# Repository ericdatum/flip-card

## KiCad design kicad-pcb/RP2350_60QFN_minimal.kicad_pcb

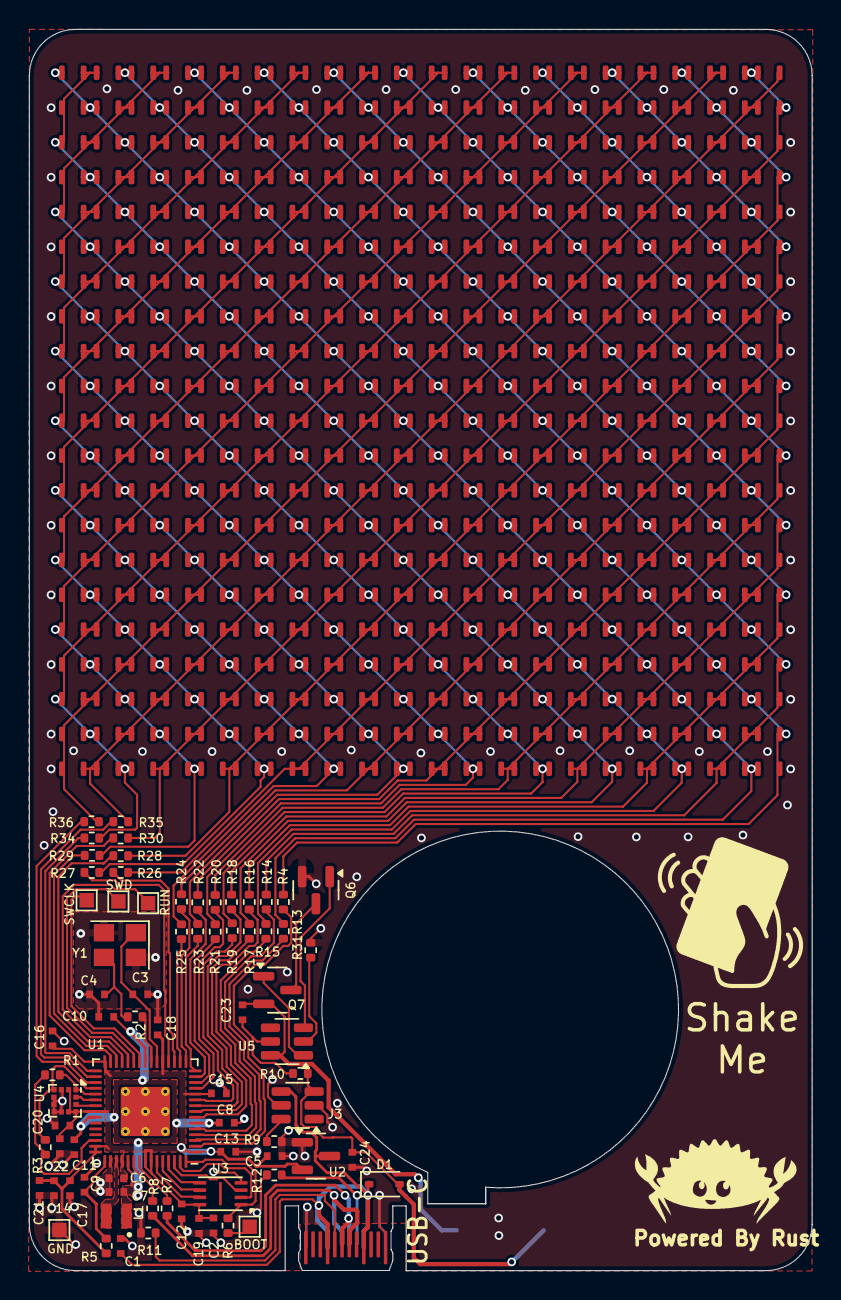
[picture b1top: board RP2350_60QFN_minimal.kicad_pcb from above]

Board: 2 copper layers, 54.0 x 85.6 mm, 517 parts (0 on the bottom side), 82 nets.

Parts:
BOOT: TestPoint; TestPoint_Pad_1.0x1.0mm
BT1: Battery_Cell; BatteryHolder_Custom
C1, C5, C24: 1u; C_0402_1005Metric_small_pads
C2, C8, C11, C12, C13, C14, C15, C16, C17, C18, C20, C21, C23: 100n; C_0402_1005Metric_small_pads
C3, C4: 15p; C_0402_1005Metric_small_pads
C6, C7, C9, C10: 4.7u; C_0402_1005Metric_small_pads
C19, C22: 10u; C_0402_1005Metric_small_pads
D1: Schottky Diode; D_SOD-323
D101, D102, D103, D104, D105, D106, D107, D108, D109, D110, D111, D112, D113, D114, D115, D116, D117, D118, D119, D120, D121, D122, D123, D124, D125, D126, D127, D128, D129, D130, D131, D132, D133, D134, D135, D136, D137, D138, D139, D140, D141, D142, D143, D144, D145, D146, D147, D148, D149, D150, D151, D152, D153, D154, D155, D156, D157, D158, D159, D160, D161, D162, D163, D164, D165, D166, D167, D168, D169, D170, D171, D172, D173, D174, D175, D176, D177, D178, D179, D180, D181, D182, D183, D184, D185, D186, D187, D188, D189, D190, D191, D192, D193, D194, D195, D196, D197, D198, D199, D200, D201, D202, D203, D204, D205, D206, D207, D208, D209, D210, D211, D212, D213, D214, D215, D216, D217, D218, D219, D220, D221, D222, D223, D224, D225, D226, D227, D228, D229, D230, D231, D232, D233, D234, D235, D236, D237, D238, D239, D240, D241, D242, D243, D244, D245, D246, D247, D248, D249, D250, D251, D252, D253, D254, D255, D256, D257, D258, D259, D260, D261, D262, D263, D264, D265, D266, D267, D268, D269, D270, D271, D272, D273, D274, D275, D276, D277, D278, D279, D280, D281, D282, D283, D284, D285, D286, D287, D288, D289, D290, D291, D292, D293, D294, D295, D296, D297, D298, D299, D300, D301, D302, D303, D304, D305, D306, D307, D308, D309, D310, D311, D312, D313, D314, D315, D316, D317, D318, D319, D320, D321, D322, D323, D324, D325, D326, D327, D328, D329, D330, D331, D332, D333, D334, D335, D336, D337, D338, D339, D340, D341, D342, D343, D344, D345, D346, D347, D348, D349, D350, D351, D352, D353, D354, D355, D356, D357, D358, D359, D360, D361, D362, D363, D364, D365, D366, D367, D368, D369, D370, D371, D372, D373, D374, D375, D376, D377, D378, D379, D380, D381, D382, D383, D384, D385, D386, D387, D388, D389, D390, D391, D392, D393, D394, D395, D396, D397, D398, D399, D400, D401, D402, D403, D404, D405, D406, D407, D408, D409, D410, D411, D412, D413, D414, D415, D416, D417, D418, D419, D420, D421, D422, D423, D424, D425, D426, D427, D428, D429, D430, D431, D432, D433, D434, D435, D436, D437, D438, D439, D440, D441, D442, D443, D444, D445, D446, D447, D448, D449, D450, D451, D452, D453, D454, D455, D456, D457, D458, D459, D460, D461, D462, D463, D464, D465, D466, D467, D468, D469, D470, D471, D472, D473, D474, D475, D476, D477, D478, D479, D480, D481, D482, D483, D484, D485, D486, D487, D488, D489, D490, D491, D492, D493, D494, D495, D496, D497, D498, D499, D500, D501, D502, D503, D504, D505, D506, D507, D508, D509, D510, D511, D512, D513, D514, D515, D516, D517, D518, D519, D520, D521, D522, D523, D524, D525, D526, D527, D528, D529, D530, D531, D532, D533, D534, D535, D536, D537, D538, D539, D540, D541: LED; LED_0603_1608Metric
GND: TestPoint; TestPoint_Pad_1.0x1.0mm
J1: USB_C_Receptacle_USB2.0_14P; USB_C_PADDLE
J3: TP4057; SOT-23-6
L1: 3.3u; L_pol_2016
Q6, Q7: HL-2302V; SOT-23
R1, R3, R11, R12: 5K1; R_0402_1005Metric
R2, R6, R31: 1K; R_0402_1005Metric
R4, R13, R14, R15, R16, R17, R18, R19, R20, R21, R22, R23, R24, R25, R26, R27, R28, R29, R30, R34, R35, R36: 22; R_0402_1005Metric
R5: 33; R_0402_1005Metric
R7, R8: 27; R_0402_1005Metric
R9: 20K; R_0402_1005Metric
R10: 100; R_0402_1005Metric
RUN: TestPoint; TestPoint_Pad_1.0x1.0mm
SWCLK: TestPoint; TestPoint_Pad_1.0x1.0mm
SWD: TestPoint; TestPoint_Pad_1.0x1.0mm
U1: RP2350A; RP2350-QFN-60-1EP_7x7_P0.4mm_EP3.4x3.4mm_ThermalVias
U2: REG_3.3V; SOT-23
U3: ZD25WQ32CEIGR; Winbond_USON-8-1EP_3x2mm_P0.5mm_EP0.2x1.6mm
U4: LIS2DH12TR; LGA-12_2x2mm_P0.5mm
U5: DW01A; SOT-23-6
Y1: ABM8-272-T3; Crystal_SMD_3225-4Pin_3.2x2.5mm

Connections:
+1V1: C7.1, C8.1, C10.1, C11.1, L1.1, U1.6 (DVDD), U1.23 (DVDD), U1.39 (DVDD), U1.50 (VREG_FB)
+3V3: C2.1, C5.1, C6.1, C12.1, C13.1, C14.1, C15.1, C16.1, C17.1, C18.1, C19.1, C20.2, C21.2, C22.1, R5.1, U1.1 (IOVDD), U1.11 (IOVDD), U1.20 (IOVDD), U1.30 (IOVDD), U1.38 (IOVDD), U1.44 (ADC_AVDD), U1.45 (IOVDD), U1.49 (VREG_VIN), U1.53 (USB_OTP_VDD), U1.54 (QSPI_IOVDD), U2.2 (VO), U3.8 (VCC), U4.2 (CS), U4.9 (VDD), U4.10 (VDD_IO)
/FLASH_SS: R6.1, U1.60 (QSPI_SS), U3.1 (~CS)
/LED_ARRAY/D1: D101.1 (K), D102.1 (K), D103.2 (A), D124.1 (K), D125.2 (A), D146.1 (K), D147.2 (A), D168.1 (K), D169.2 (A), D190.1 (K), D191.2 (A), D212.1 (K), D213.2 (A), D234.1 (K), D235.2 (A), D256.1 (K), D257.2 (A), D278.1 (K), D279.2 (A), D300.1 (K), D301.2 (A), D322.1 (K), D323.2 (A), D344.1 (K), D345.2 (A), D366.1 (K), D367.2 (A), D388.1 (K), D389.2 (A), D410.1 (K), D411.2 (A), D432.1 (K), D433.2 (A), D454.1 (K), D455.2 (A), D476.1 (K), D477.2 (A), D498.1 (K), D499.2 (A), D520.1 (K), R36.1
/LED_ARRAY/D2: D101.2 (A), D122.1 (K), D123.2 (A), D144.1 (K), D145.2 (A), D166.1 (K), D167.2 (A), D188.1 (K), D189.2 (A), D210.1 (K), D211.2 (A), D232.1 (K), D233.2 (A), D254.1 (K), D255.2 (A), D276.1 (K), D277.2 (A), D298.1 (K), D299.2 (A), D320.1 (K), D321.2 (A), D342.1 (K), D343.2 (A), D364.1 (K), D365.2 (A), D386.1 (K), D387.2 (A), D408.1 (K), D409.2 (A), D430.1 (K), D431.2 (A), D452.1 (K), D453.2 (A), D474.1 (K), D475.2 (A), D496.1 (K), D497.2 (A), D518.1 (K), D519.2 (A), D540.1 (K), D541.2 (A), R35.1
/LED_ARRAY/D3: D102.2 (A), D103.1 (K), D104.1 (K), D105.2 (A), D122.2 (A), D123.1 (K), D126.1 (K), D127.2 (A), D143.1 (K), D148.1 (K), D149.2 (A), D170.1 (K), D171.2 (A), D192.1 (K), D193.2 (A), D214.1 (K), D215.2 (A), D236.1 (K), D237.2 (A), D258.1 (K), D259.2 (A), D280.1 (K), D281.2 (A), D302.1 (K), D303.2 (A), D324.1 (K), D325.2 (A), D346.1 (K), D347.2 (A), D368.1 (K), D369.2 (A), D390.1 (K), D391.2 (A), D412.1 (K), D413.2 (A), D434.1 (K), D435.2 (A), D456.1 (K), D457.2 (A), D478.1 (K), R34.1
/LED_ARRAY/D4: D143.2 (A), D164.1 (K), D165.2 (A), D186.1 (K), D187.2 (A), D208.1 (K), D209.2 (A), D230.1 (K), D231.2 (A), D252.1 (K), D253.2 (A), D274.1 (K), D275.2 (A), D296.1 (K), D297.2 (A), D318.1 (K), D319.2 (A), D340.1 (K), D341.2 (A), D362.1 (K), D363.2 (A), D384.1 (K), D385.2 (A), D406.1 (K), D407.2 (A), D428.1 (K), D429.2 (A), D450.1 (K), D451.2 (A), D472.1 (K), D473.2 (A), D494.1 (K), D495.2 (A), D516.1 (K), D517.2 (A), D520.2 (A), D538.1 (K), D539.2 (A), D540.2 (A), D541.1 (K), R30.1
/LED_ARRAY/D5: D104.2 (A), D105.1 (K), D106.1 (K), D107.2 (A), D124.2 (A), D125.1 (K), D128.1 (K), D129.2 (A), D144.2 (A), D145.1 (K), D150.1 (K), D151.2 (A), D164.2 (A), D165.1 (K), D172.1 (K), D173.2 (A), D185.1 (K), D194.1 (K), D195.2 (A), D216.1 (K), D217.2 (A), D238.1 (K), D239.2 (A), D260.1 (K), D261.2 (A), D282.1 (K), D283.2 (A), D304.1 (K), D305.2 (A), D326.1 (K), D327.2 (A), D348.1 (K), D349.2 (A), D370.1 (K), D371.2 (A), D392.1 (K), D393.2 (A), D414.1 (K), D415.2 (A), D436.1 (K), R29.1
/LED_ARRAY/D6: D185.2 (A), D206.1 (K), D207.2 (A), D228.1 (K), D229.2 (A), D250.1 (K), D251.2 (A), D272.1 (K), D273.2 (A), D294.1 (K), D295.2 (A), D316.1 (K), D317.2 (A), D338.1 (K), D339.2 (A), D360.1 (K), D361.2 (A), D382.1 (K), D383.2 (A), D404.1 (K), D405.2 (A), D426.1 (K), D427.2 (A), D448.1 (K), D449.2 (A), D470.1 (K), D471.2 (A), D478.2 (A), D492.1 (K), D493.2 (A), D498.2 (A), D499.1 (K), D514.1 (K), D515.2 (A), D518.2 (A), D519.1 (K), D536.1 (K), D537.2 (A), D538.2 (A), D539.1 (K), R28.1
/LED_ARRAY/D7: D106.2 (A), D107.1 (K), D108.1 (K), D109.2 (A), D126.2 (A), D127.1 (K), D130.1 (K), D131.2 (A), D146.2 (A), D147.1 (K), D152.1 (K), D153.2 (A), D166.2 (A), D167.1 (K), D174.1 (K), D175.2 (A), D186.2 (A), D187.1 (K), D196.1 (K), D197.2 (A), D206.2 (A), D207.1 (K), D218.1 (K), D219.2 (A), D227.1 (K), D240.1 (K), D241.2 (A), D262.1 (K), D263.2 (A), D284.1 (K), D285.2 (A), D306.1 (K), D307.2 (A), D328.1 (K), D329.2 (A), D350.1 (K), D351.2 (A), D372.1 (K), D373.2 (A), D394.1 (K), R27.1
/LED_ARRAY/D8: D227.2 (A), D248.1 (K), D249.2 (A), D270.1 (K), D271.2 (A), D292.1 (K), D293.2 (A), D314.1 (K), D315.2 (A), D336.1 (K), D337.2 (A), D358.1 (K), D359.2 (A), D380.1 (K), D381.2 (A), D402.1 (K), D403.2 (A), D424.1 (K), D425.2 (A), D436.2 (A), D446.1 (K), D447.2 (A), D456.2 (A), D457.1 (K), D468.1 (K), D469.2 (A), D476.2 (A), D477.1 (K), D490.1 (K), D491.2 (A), D496.2 (A), D497.1 (K), D512.1 (K), D513.2 (A), D516.2 (A), D517.1 (K), D534.1 (K), D535.2 (A), D536.2 (A), D537.1 (K), R26.1
/LED_ARRAY/D9: D108.2 (A), D109.1 (K), D110.1 (K), D111.2 (A), D128.2 (A), D129.1 (K), D132.1 (K), D133.2 (A), D148.2 (A), D149.1 (K), D154.1 (K), D155.2 (A), D168.2 (A), D169.1 (K), D176.1 (K), D177.2 (A), D188.2 (A), D189.1 (K), D198.1 (K), D199.2 (A), D208.2 (A), D209.1 (K), D220.1 (K), D221.2 (A), D228.2 (A), D229.1 (K), D242.1 (K), D243.2 (A), D248.2 (A), D249.1 (K), D264.1 (K), D265.2 (A), D269.1 (K), D286.1 (K), D287.2 (A), D308.1 (K), D309.2 (A), D330.1 (K), D331.2 (A), D352.1 (K), R25.1
/LED_ARRAY/D10: D269.2 (A), D290.1 (K), D291.2 (A), D312.1 (K), D313.2 (A), D334.1 (K), D335.2 (A), D356.1 (K), D357.2 (A), D378.1 (K), D379.2 (A), D394.2 (A), D400.1 (K), D401.2 (A), D414.2 (A), D415.1 (K), D422.1 (K), D423.2 (A), D434.2 (A), D435.1 (K), D444.1 (K), D445.2 (A), D454.2 (A), D455.1 (K), D466.1 (K), D467.2 (A), D474.2 (A), D475.1 (K), D488.1 (K), D489.2 (A), D494.2 (A), D495.1 (K), D510.1 (K), D511.2 (A), D514.2 (A), D515.1 (K), D532.1 (K), D533.2 (A), D534.2 (A), D535.1 (K), R24.1
/LED_ARRAY/D11: D110.2 (A), D111.1 (K), D112.1 (K), D113.2 (A), D130.2 (A), D131.1 (K), D134.1 (K), D135.2 (A), D150.2 (A), D151.1 (K), D156.1 (K), D157.2 (A), D170.2 (A), D171.1 (K), D178.1 (K), D179.2 (A), D190.2 (A), D191.1 (K), D200.1 (K), D201.2 (A), D210.2 (A), D211.1 (K), D222.1 (K), D223.2 (A), D230.2 (A), D231.1 (K), D244.1 (K), D245.2 (A), D250.2 (A), D251.1 (K), D266.1 (K), D267.2 (A), D270.2 (A), D271.1 (K), D288.1 (K), D289.2 (A), D290.2 (A), D291.1 (K), D310.1 (K), D311.1 (K), R23.1
/LED_ARRAY/D12: D311.2 (A), D332.1 (K), D333.2 (A), D352.2 (A), D354.1 (K), D355.2 (A), D372.2 (A), D373.1 (K), D376.1 (K), D377.2 (A), D392.2 (A), D393.1 (K), D398.1 (K), D399.2 (A), D412.2 (A), D413.1 (K), D420.1 (K), D421.2 (A), D432.2 (A), D433.1 (K), D442.1 (K), D443.2 (A), D452.2 (A), D453.1 (K), D464.1 (K), D465.2 (A), D472.2 (A), D473.1 (K), D486.1 (K), D487.2 (A), D492.2 (A), D493.1 (K), D508.1 (K), D509.2 (A), D512.2 (A), D513.1 (K), D530.1 (K), D531.2 (A), D532.2 (A), D533.1 (K), R22.1
/LED_ARRAY/D13: D112.2 (A), D113.1 (K), D114.1 (K), D115.2 (A), D132.2 (A), D133.1 (K), D136.1 (K), D137.2 (A), D152.2 (A), D153.1 (K), D158.1 (K), D159.2 (A), D172.2 (A), D173.1 (K), D180.1 (K), D181.2 (A), D192.2 (A), D193.1 (K), D202.1 (K), D203.2 (A), D212.2 (A), D213.1 (K), D224.1 (K), D225.2 (A), D232.2 (A), D233.1 (K), D246.1 (K), D247.2 (A), D252.2 (A), D253.1 (K), D268.1 (K), D272.2 (A), D273.1 (K), D292.2 (A), D293.1 (K), D312.2 (A), D313.1 (K), D332.2 (A), D333.1 (K), D353.1 (K), R21.1
/LED_ARRAY/D14: D310.2 (A), D330.2 (A), D331.1 (K), D350.2 (A), D351.1 (K), D353.2 (A), D370.2 (A), D371.1 (K), D374.1 (K), D375.2 (A), D390.2 (A), D391.1 (K), D396.1 (K), D397.2 (A), D410.2 (A), D411.1 (K), D418.1 (K), D419.2 (A), D430.2 (A), D431.1 (K), D440.1 (K), D441.2 (A), D450.2 (A), D451.1 (K), D462.1 (K), D463.2 (A), D470.2 (A), D471.1 (K), D484.1 (K), D485.2 (A), D490.2 (A), D491.1 (K), D506.1 (K), D507.2 (A), D510.2 (A), D511.1 (K), D528.1 (K), D529.2 (A), D530.2 (A), D531.1 (K), R20.1
/LED_ARRAY/D15: D114.2 (A), D115.1 (K), D116.1 (K), D117.2 (A), D134.2 (A), D135.1 (K), D138.1 (K), D139.2 (A), D154.2 (A), D155.1 (K), D160.1 (K), D161.2 (A), D174.2 (A), D175.1 (K), D182.1 (K), D183.2 (A), D194.2 (A), D195.1 (K), D204.1 (K), D205.2 (A), D214.2 (A), D215.1 (K), D226.1 (K), D234.2 (A), D235.1 (K), D254.2 (A), D255.1 (K), D274.2 (A), D275.1 (K), D294.2 (A), D295.1 (K), D314.2 (A), D315.1 (K), D334.2 (A), D335.1 (K), D354.2 (A), D355.1 (K), D374.2 (A), D375.1 (K), D395.1 (K), R19.1
/LED_ARRAY/D16: D268.2 (A), D288.2 (A), D289.1 (K), D308.2 (A), D309.1 (K), D328.2 (A), D329.1 (K), D348.2 (A), D349.1 (K), D368.2 (A), D369.1 (K), D388.2 (A), D389.1 (K), D395.2 (A), D408.2 (A), D409.1 (K), D416.1 (K), D417.2 (A), D428.2 (A), D429.1 (K), D438.1 (K), D439.2 (A), D448.2 (A), D449.1 (K), D460.1 (K), D461.2 (A), D468.2 (A), D469.1 (K), D482.1 (K), D483.2 (A), D488.2 (A), D489.1 (K), D504.1 (K), D505.2 (A), D508.2 (A), D509.1 (K), D526.1 (K), D527.2 (A), D528.2 (A), D529.1 (K), R18.1
/LED_ARRAY/D17: D116.2 (A), D117.1 (K), D118.1 (K), D119.2 (A), D136.2 (A), D137.1 (K), D140.1 (K), D141.2 (A), D156.2 (A), D157.1 (K), D162.1 (K), D163.2 (A), D176.2 (A), D177.1 (K), D184.1 (K), D196.2 (A), D197.1 (K), D216.2 (A), D217.1 (K), D236.2 (A), D237.1 (K), D256.2 (A), D257.1 (K), D276.2 (A), D277.1 (K), D296.2 (A), D297.1 (K), D316.2 (A), D317.1 (K), D336.2 (A), D337.1 (K), D356.2 (A), D357.1 (K), D376.2 (A), D377.1 (K), D396.2 (A), D397.1 (K), D416.2 (A), D417.1 (K), D437.1 (K), R17.1
/LED_ARRAY/D18: D226.2 (A), D246.2 (A), D247.1 (K), D266.2 (A), D267.1 (K), D286.2 (A), D287.1 (K), D306.2 (A), D307.1 (K), D326.2 (A), D327.1 (K), D346.2 (A), D347.1 (K), D366.2 (A), D367.1 (K), D386.2 (A), D387.1 (K), D406.2 (A), D407.1 (K), D426.2 (A), D427.1 (K), D437.2 (A), D446.2 (A), D447.1 (K), D458.1 (K), D459.2 (A), D466.2 (A), D467.1 (K), D480.1 (K), D481.2 (A), D486.2 (A), D487.1 (K), D502.1 (K), D503.2 (A), D506.2 (A), D507.1 (K), D524.1 (K), D525.2 (A), D526.2 (A), D527.1 (K), R16.1
/LED_ARRAY/D19: D118.2 (A), D119.1 (K), D120.1 (K), D121.2 (A), D138.2 (A), D139.1 (K), D142.1 (K), D158.2 (A), D159.1 (K), D178.2 (A), D179.1 (K), D198.2 (A), D199.1 (K), D218.2 (A), D219.1 (K), D238.2 (A), D239.1 (K), D258.2 (A), D259.1 (K), D278.2 (A), D279.1 (K), D298.2 (A), D299.1 (K), D318.2 (A), D319.1 (K), D338.2 (A), D339.1 (K), D358.2 (A), D359.1 (K), D378.2 (A), D379.1 (K), D398.2 (A), D399.1 (K), D418.2 (A), D419.1 (K), D438.2 (A), D439.1 (K), D458.2 (A), D459.1 (K), D479.1 (K), R15.1
/LED_ARRAY/D20: D184.2 (A), D204.2 (A), D205.1 (K), D224.2 (A), D225.1 (K), D244.2 (A), D245.1 (K), D264.2 (A), D265.1 (K), D284.2 (A), D285.1 (K), D304.2 (A), D305.1 (K), D324.2 (A), D325.1 (K), D344.2 (A), D345.1 (K), D364.2 (A), D365.1 (K), D384.2 (A), D385.1 (K), D404.2 (A), D405.1 (K), D424.2 (A), D425.1 (K), D444.2 (A), D445.1 (K), D464.2 (A), D465.1 (K), D479.2 (A), D484.2 (A), D485.1 (K), D500.1 (K), D501.2 (A), D504.2 (A), D505.1 (K), D522.1 (K), D523.2 (A), D524.2 (A), D525.1 (K), R14.1
/LED_ARRAY/D21: D120.2 (A), D121.1 (K), D140.2 (A), D141.1 (K), D160.2 (A), D161.1 (K), D180.2 (A), D181.1 (K), D200.2 (A), D201.1 (K), D220.2 (A), D221.1 (K), D240.2 (A), D241.1 (K), D260.2 (A), D261.1 (K), D280.2 (A), D281.1 (K), D300.2 (A), D301.1 (K), D320.2 (A), D321.1 (K), D340.2 (A), D341.1 (K), D360.2 (A), D361.1 (K), D380.2 (A), D381.1 (K), D400.2 (A), D401.1 (K), D420.2 (A), D421.1 (K), D440.2 (A), D441.1 (K), D460.2 (A), D461.1 (K), D480.2 (A), D481.1 (K), D500.2 (A), D501.1 (K), D521.1 (K), R13.1
/LED_ARRAY/D22: D142.2 (A), D162.2 (A), D163.1 (K), D182.2 (A), D183.1 (K), D202.2 (A), D203.1 (K), D222.2 (A), D223.1 (K), D242.2 (A), D243.1 (K), D262.2 (A), D263.1 (K), D282.2 (A), D283.1 (K), D302.2 (A), D303.1 (K), D322.2 (A), D323.1 (K), D342.2 (A), D343.1 (K), D362.2 (A), D363.1 (K), D382.2 (A), D383.1 (K), D402.2 (A), D403.1 (K), D422.2 (A), D423.1 (K), D442.2 (A), D443.1 (K), D462.2 (A), D463.1 (K), D482.2 (A), D483.1 (K), D502.2 (A), D503.1 (K), D521.2 (A), D522.2 (A), D523.1 (K), R4.1
/QSPI_SCLK: U1.56 (QSPI_SCLK), U3.6 (CLK)
/QSPI_SD0: U1.57 (QSPI_SD0), U3.5 (DI(IO0))
/QSPI_SD1: U1.59 (QSPI_SD1), U3.2 (DO(IO1))
/QSPI_SD2: U1.58 (QSPI_SD2), U3.3 (IO2)
/QSPI_SD3: U1.55 (QSPI_SD3), U3.7 (IO3)
/USB_D+: J1.A6 (D+), J1.B6 (D+), R7.1
/USB_D-: J1.A7 (D-), J1.B7 (D-), R8.1
/VREG_AVDD: C9.1, R5.2, U1.46 (VREG_AVDD)
/VREG_LX: L1.2, U1.48 (VREG_LX)
/XIN: C3.1, U1.21 (XIN), Y1.1
/XOUT: R2.1, U1.22 (XOUT)
ACCEL INTERRPUT 1: U1.36 (GPIO24), U4.12 (INT1)
ACCEL INTERRUPT 2: U1.37 (GPIO25), U4.11 (INT2)
ENABLE_ACCEL: R1.2, R3.2, U1.43 (GPIO29_ADC3)
GND: C1.2, C2.2, C3.2, C4.2, C5.2, C6.2, C7.2, C8.2, C9.2, C10.2, C11.2, C12.2, C13.2, C14.2, C15.2, C16.2, C17.2, C18.2, C19.2, C20.1, C21.1, C22.2, C24.2, GND.1, J1.A1 (GND), J1.A12 (GND), J1.B1 (GND), J1.B12 (GND), J3.2 (GND), J3.5 (STDBY), Q6.2 (S), R9.2, R11.2, R12.2, R31.1, U1.47 (VREG_PGND), U1.61 (GND), U2.1 (GND), U3.4 (GND), U4.3 (SDO/SAO), U4.5 (RES), U4.6 (GND), U4.7 (GND__1), U4.8 (GND__2), Y1.2, Y1.4
I2C1_SCL: R1.1, U1.35 (GPIO23), U4.1 (SCL/SPC)
I2C1_SDA: R3.1, U1.34 (GPIO22), U4.4 (SDA/SDI/SDO)
unnamed: BOOT.1, R6.2
unnamed: BT1.1 (+), C24.1, D1.2 (A), J3.3 (BAT), R10.1
unnamed: BT1.2 (-), C23.2, Q7.2 (S), U5.6 (GND)
unnamed: C4.1, R2.2, Y1.3
unnamed: J1.A5 (CC1), R11.1
unnamed: J1.B5 (CC2), R12.1
unnamed: J3.6 (PROG), R9.1
unnamed: Q6.3 (D), Q7.3 (D)
unnamed: Q6.1 (G), U5.3 (OC)
unnamed: Q7.1 (G), U5.1 (OD)
unnamed: R4.2, U1.2 (GPIO0)
unnamed: R13.2, U1.3 (GPIO1)
unnamed: R14.2, U1.4 (GPIO2)
unnamed: R15.2, U1.5 (GPIO3)
unnamed: R16.2, U1.7 (GPIO4)
unnamed: R17.2, U1.8 (GPIO5)
unnamed: R18.2, U1.9 (GPIO6)
unnamed: R19.2, U1.10 (GPIO7)
unnamed: R20.2, U1.12 (GPIO8)
unnamed: R21.2, U1.13 (GPIO9)
unnamed: R22.2, U1.14 (GPIO10)
unnamed: R23.2, U1.15 (GPIO11)
unnamed: R24.2, U1.16 (GPIO12)
unnamed: R25.2, U1.17 (GPIO13)
unnamed: R26.2, U1.18 (GPIO14)
unnamed: R27.2, U1.19 (GPIO15)
unnamed: R28.2, U1.27 (GPIO16)
unnamed: R29.2, U1.28 (GPIO17)
unnamed: R30.2, U1.29 (GPIO18)
unnamed: R34.2, U1.31 (GPIO19)
unnamed: R35.2, U1.32 (GPIO20)
unnamed: R36.2, U1.33 (GPIO21)
unnamed: RUN.1, U1.26 (RUN)
unnamed: SWCLK.1, U1.24 (SWCLK)
unnamed: SWD.1, U1.25 (SWD)
unnamed: R8.2, U1.51 (USB_DM)
unnamed: R7.2, U1.52 (USB_DP)
unnamed: R31.2, U5.2 (CS)
unnamed: C23.1, R10.2, U5.5 (VCC)
VBUS: C1.1, D1.1 (K), J1.A4 (VBUS), J1.A9 (VBUS), J1.B4 (VBUS), J1.B9 (VBUS), J3.4 (VCC), U2.3 (VI)

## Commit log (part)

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2026-04-01 DrillSense business card adaptation
    - Replace back silkscreen text: Nick Johnson -> Eric Datum, Embedded Design -> DRILLSENSE, contact info -> drillsense.com
    - Fix critical pressure solver bug in fluid_sim_crate (line 1026: self.u -> self.v, += -> -=)
    - Add DrillSense ≠ mark startup animation (3-second display before fluid sim starts)
